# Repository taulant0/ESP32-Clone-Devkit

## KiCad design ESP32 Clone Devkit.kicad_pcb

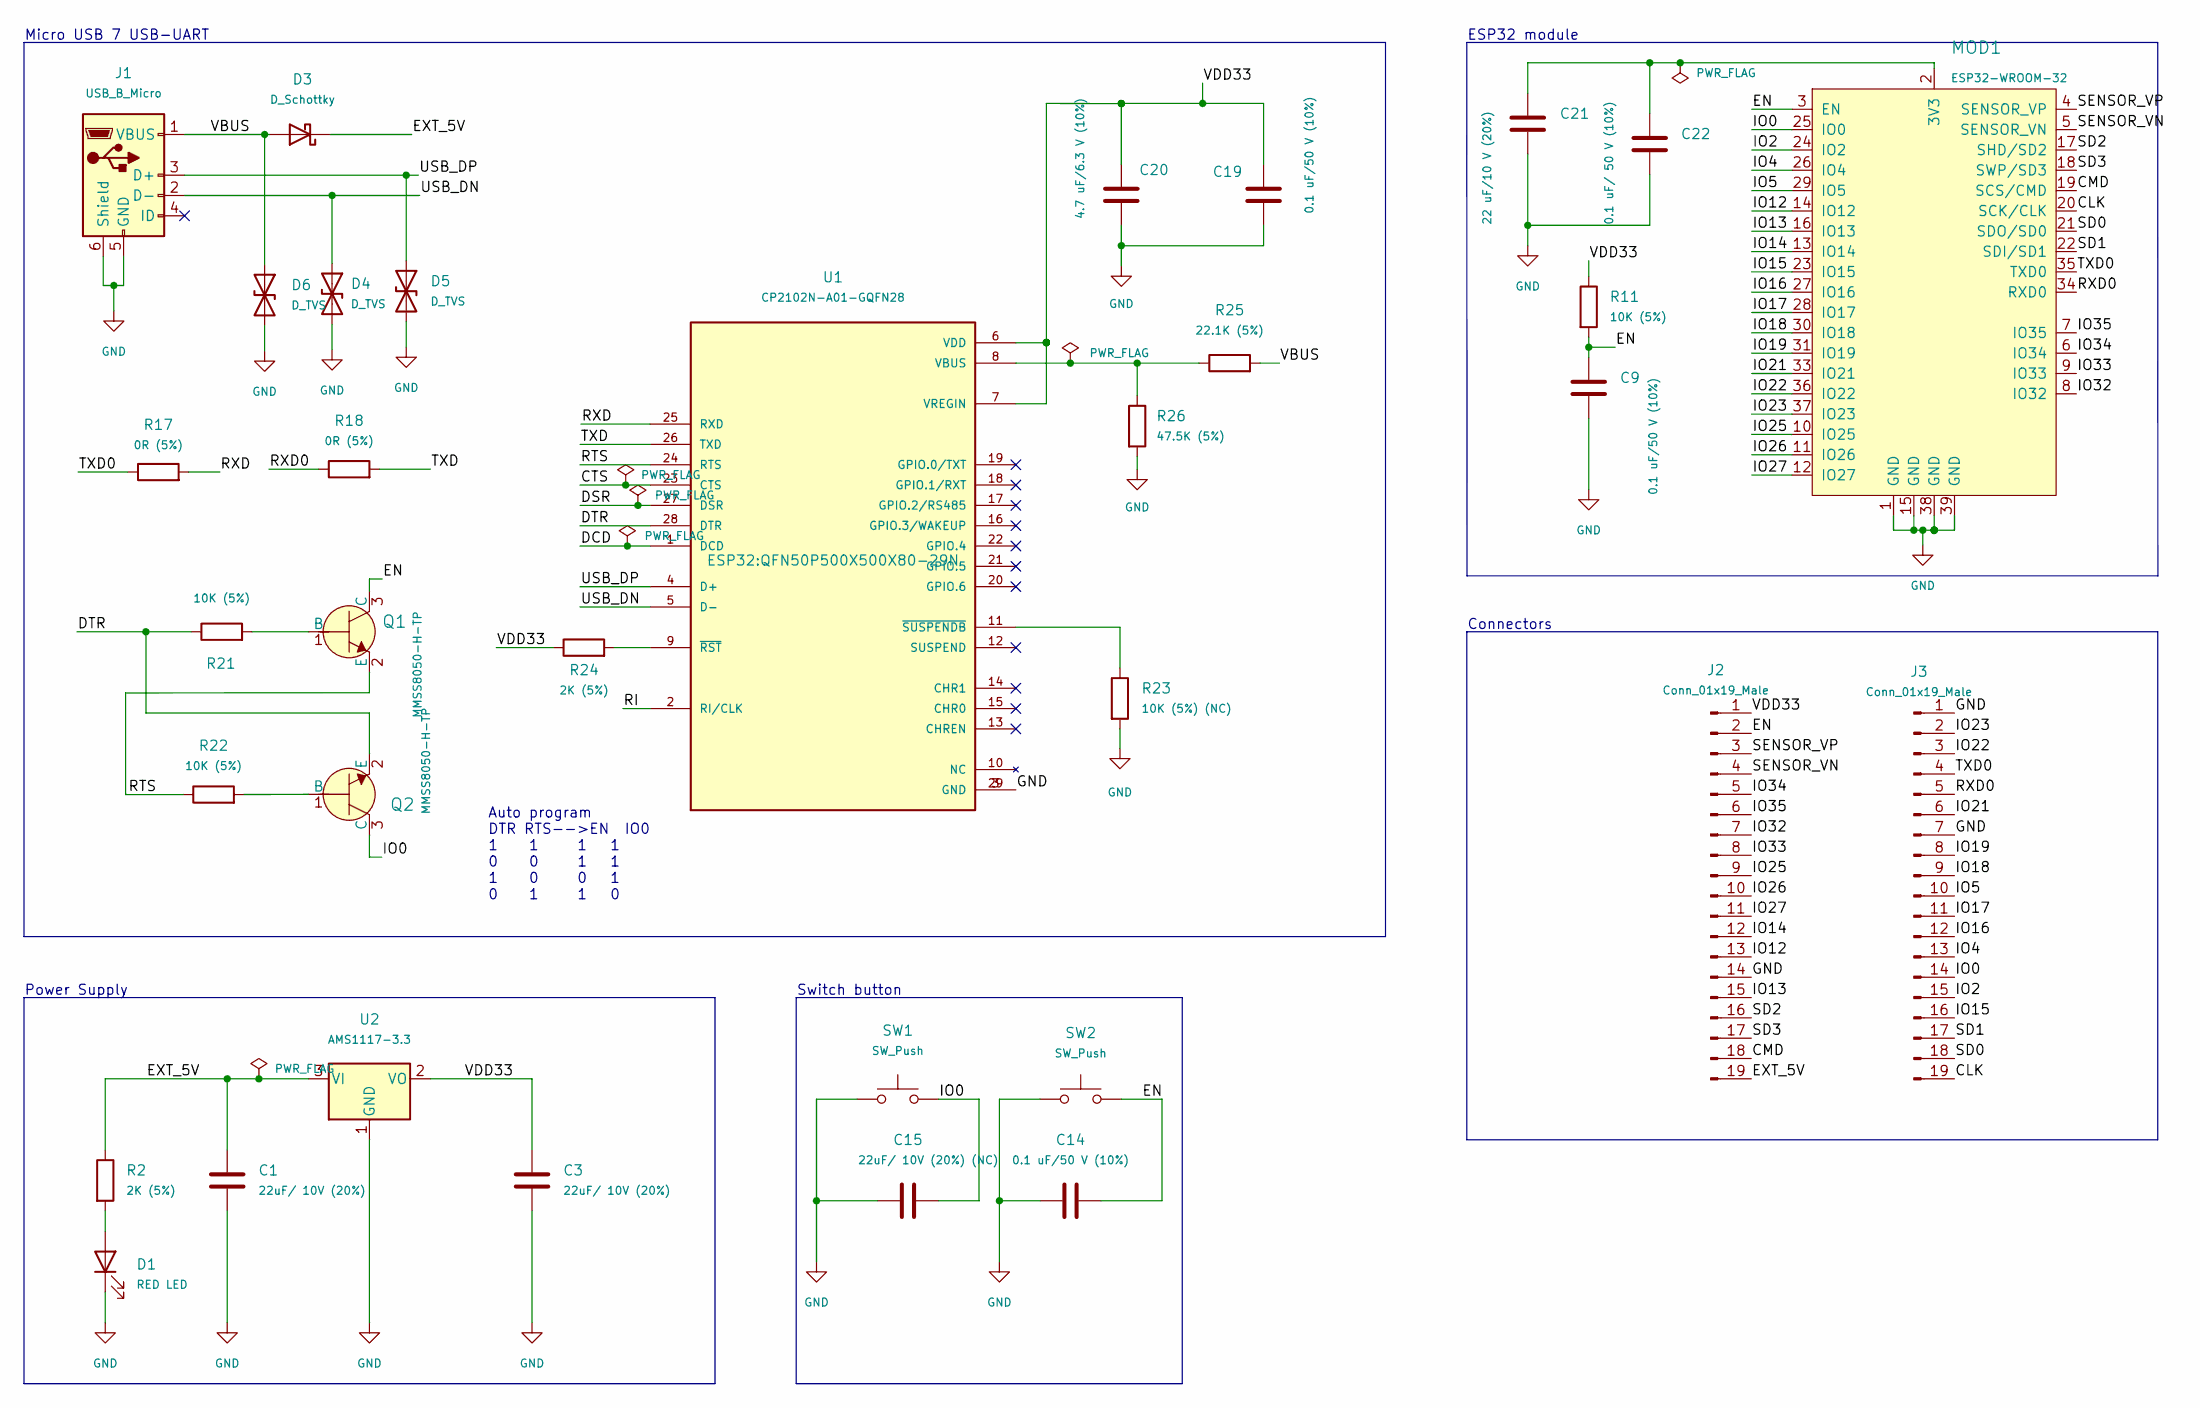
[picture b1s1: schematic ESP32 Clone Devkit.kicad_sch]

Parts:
C1, C3: 22uF/ 10V (20%); C_0201_0603Metric
C9, C14, C19: 0.1 uF/50 V (10%); C_01005_0402Metric
C15: 22uF/ 10V (20%) (NC); C_01005_0402Metric
C20: 4.7 uF/6.3 V (10%); C_01005_0402Metric
C21: 22 uF/10 V (20%); C_01005_0402Metric
C22: 0.1 uF/ 50 V (10%); C_01005_0402Metric
D1: RED LED; LED_0603_1608Metric
D3: D_Schottky; D_SOD-323
D4, D5, D6: D_TVS; D_SOD-523
J1: USB_B_Micro; USB_Micro-AB_Molex_47590-0001
J2, J3: Conn_01x19_Male; PinHeader_1x19_P2.54mm_Vertical
MOD1: ESP32-WROOM-32; ESP32-WROOM-32D; MPN ESP32-WROOM-32; Digi-Key_PN 1904-1010-1-ND
Q1, Q2: MMSS8050-H-TP; SOT-23-3; MPN MMSS8050-H-TP; Digi-Key_PN MMSS8050-H-TPMSCT-ND
R2, R24: 2K (5%); R_01005_0402Metric
R11, R21, R22: 10K (5%); R_01005_0402Metric
R17, R18: 0R (5%); R_01005_0402Metric
R23: 10K (5%) (NC); R_01005_0402Metric
R25: 22.1K (5%); R_01005_0402Metric
R26: 47.5K (5%); R_01005_0402Metric
SW1, SW2: SW_Push; SW_SPST_B3S-1000
U1: CP2102N-A01-GQFN28; QFN50P500X500X80-29N; PARTREV 1.0
U2: AMS1117-3.3; SOT-223-3_TabPin2

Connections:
/CLK: J3.19, MOD1.20 (SCK/CLK)
/CMD: J2.18, MOD1.19 (SCS/CMD)
/CTS: U1.23 (CTS)
/DCD: U1.1 (DCD)
/DSR: U1.27 (DSR)
/DTR: Q2.2 (E), R21.1, U1.28 (DTR)
/EN: C9.2, C14.2, J2.2, MOD1.3 (EN), Q1.3 (C), R11.2, SW2.2
/EXT_5V: C1.1, D3.1 (K), J2.19, R2.1, U2.3 (VI)
/IO0: C15.2, J3.14, MOD1.25 (IO0), Q2.3 (C), SW1.2
/IO2: J3.15, MOD1.24 (IO2)
/IO4: J3.13, MOD1.26 (IO4)
/IO5: J3.10, MOD1.29 (IO5)
/IO12: J2.13, MOD1.14 (IO12)
/IO13: J2.15, MOD1.16 (IO13)
/IO14: J2.12, MOD1.13 (IO14)
/IO15: J3.16, MOD1.23 (IO15)
/IO16: J3.12, MOD1.27 (IO16)
/IO17: J3.11, MOD1.28 (IO17)
/IO18: J3.9, MOD1.30 (IO18)
/IO19: J3.8, MOD1.31 (IO19)
/IO21: J3.6, MOD1.33 (IO21)
/IO22: J3.3, MOD1.36 (IO22)
/IO23: J3.2, MOD1.37 (IO23)
/IO25: J2.9, MOD1.10 (IO25)
/IO26: J2.10, MOD1.11 (IO26)
/IO27: J2.11, MOD1.12 (IO27)
/IO32: J2.7, MOD1.8 (IO32)
/IO33: J2.8, MOD1.9 (IO33)
/IO34: J2.5, MOD1.6 (IO34)
/IO35: J2.6, MOD1.7 (IO35)
/RI: U1.2 (RI/CLK)
/RTS: Q1.2 (E), R22.1, U1.24 (RTS)
/RXD: R17.2, U1.25 (RXD)
/RXD0: J3.5, MOD1.34 (RXD0), R18.1
/SD0: J3.18, MOD1.21 (SDO/SD0)
/SD1: J3.17, MOD1.22 (SDI/SD1)
/SD2: J2.16, MOD1.17 (SHD/SD2)
/SD3: J2.17, MOD1.18 (SWP/SD3)
/SENSOR_VN: J2.4, MOD1.5 (SENSOR_VN)
/SENSOR_VP: J2.3, MOD1.4 (SENSOR_VP)
/TXD: R18.2, U1.26 (TXD)
/TXD0: J3.4, MOD1.35 (TXD0), R17.1
/USB_DN: D4.1 (A1), J1.2 (D-), U1.5 (D-)
/USB_DP: D5.1 (A1), J1.3 (D+), U1.4 (D+)
/VBUS: D3.2 (A), D6.1 (A1), J1.1 (VBUS), R25.2
/VDD33: C3.1, C19.1, C20.1, J2.1, R11.1, R24.1, U1.6 (VDD), U1.7 (VREGIN), U2.2 (VO)
GND: C1.2, C3.2, C9.1, C14.1, C15.1, C19.2, C20.2, C21.2, C22.1, D1.1 (K), D4.2 (A2), D5.2 (A2), D6.2 (A2), J1.5 (GND), J1.6 (Shield), J2.14, J3.1, J3.7, MOD1.1 (GND), MOD1.15 (GND), MOD1.38 (GND), MOD1.39 (GND), R23.2, R26.2, SW1.1, SW2.1, U1.3 (GND), U1.29 (GND), U2.1 (GND)
unnamed: C21.1, C22.2, MOD1.2 (3V3)
unnamed: D1.2 (A), R2.2
unnamed: Q1.1 (B), R21.2
unnamed: Q2.1 (B), R22.2
unnamed: R23.1, U1.11 (~SUSPENDB)
unnamed: R24.2, U1.9 (~RST)
unnamed: R25.1, R26.1, U1.8 (VBUS)

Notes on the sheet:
Connectors
Switch button
Micro USB 7 USB-UART
ESP32 module
Auto program DTR RTS-->EN IO0 1 1 1 1 0 0 1 1 1 0 0 1 0 1 1 0
Power Supply

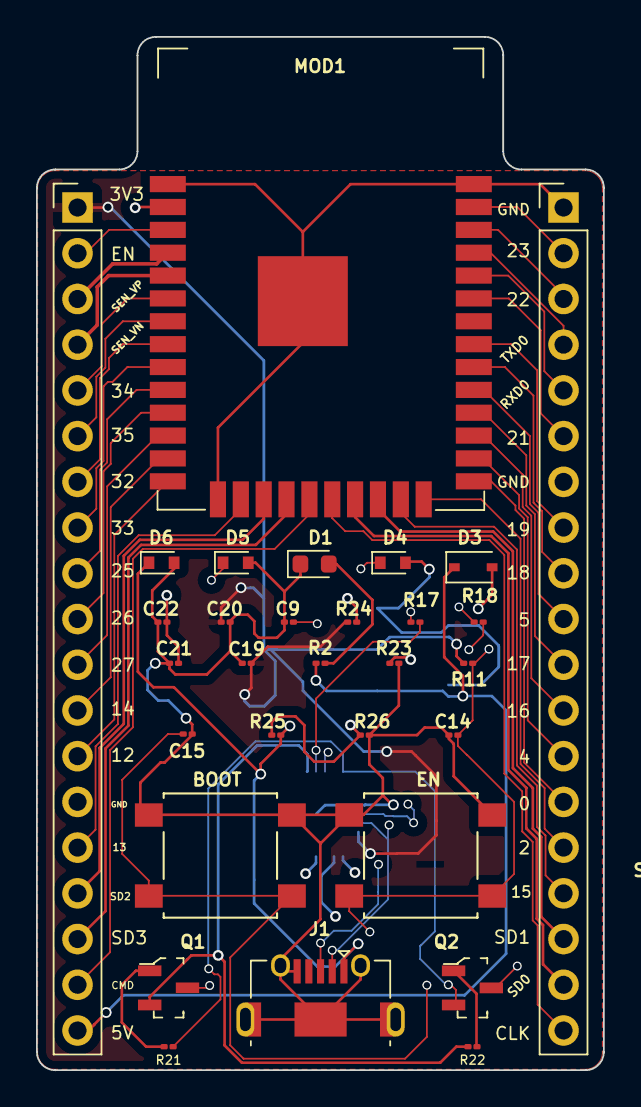
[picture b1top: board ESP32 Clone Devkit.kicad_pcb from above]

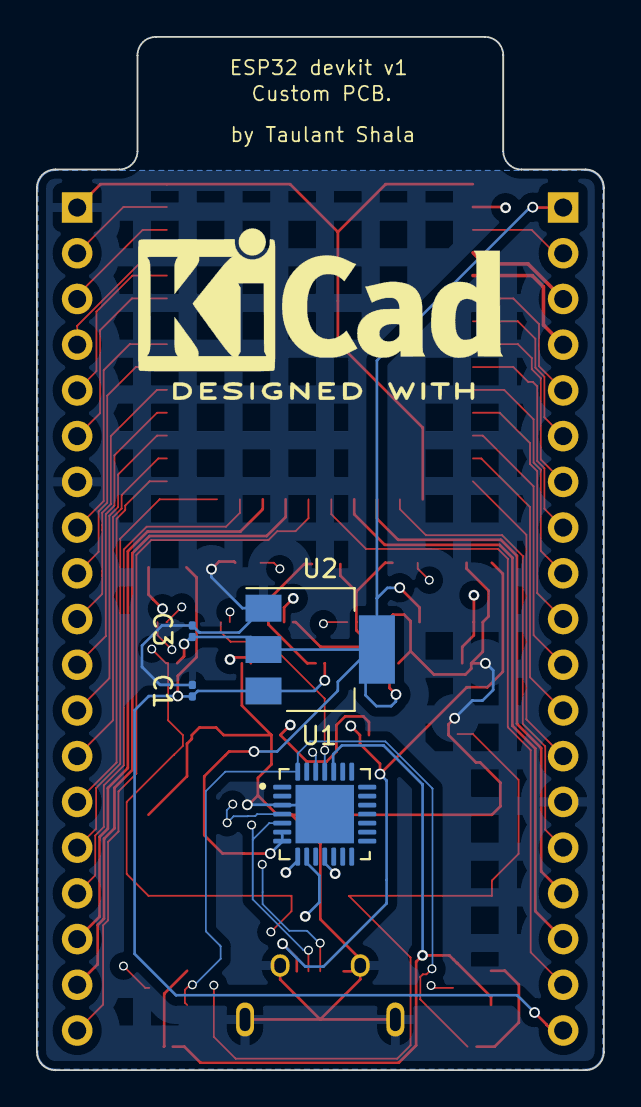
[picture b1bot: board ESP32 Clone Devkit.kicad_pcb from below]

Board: 4 copper layers, 31.5 x 57.4 mm, 34 parts (4 on the bottom side), 50 nets.

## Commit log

2025-05-24 first commit - final project.
2025-05-25 Added downloadble files.
